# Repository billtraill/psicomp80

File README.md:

# PSI COMP80

**The web pages: [billtraill.github.io/psicomp80](https://billtraill.github.io/psicomp80/)**: screens, an emulator to run in your browser, annotated ROM listings, a LISP, and the hardware in three versions.

The PSI COMP80 is a Z80 computer designed by J. H. Adams. It was published as a build-it-yourself series, "A scientific computer", in *Wireless World* from April to September 1979, and Powertran sold it as a kit. It has a 64 × 32 character screen, an MM57109 calculator chip for its arithmetic, and BURP, a calculator language, in 3 KB of ROM.

This repository brings it back:
- a MAME driver;
- the ROM, disassembled and annotated;
- twenty more ROMs written for it: FORTH, LISP, Tiny BASIC, Logo, CHIP-8, FOCAL, PILOT, a Z80 assembler and disassembler (ZASM), Prolog, VTL-2, Mouse, Befunge, a spreadsheet (CALC), TRAC, a PL/0 compiler, BF, a line editor (ED), a card-file database (FILE), an adventure engine (QUEST) and APL;
- its programs and the 1980 floppy disc system;
- a web emulator;
- the original board redrawn in KiCad, plus two new versions that run the same ROMs on current parts.

## The web pages

| Page | What it is |
|---|---|
| [PSI COMP80 Screens](https://billtraill.github.io/psicomp80/screenshots.html) | What it looked like: the monitor, BURP, FORTH, LISP, the Game of Life, the articles' pictures |
| [Emulator](https://billtraill.github.io/psicomp80/emulator.html) | The COMP80 in the browser, with all twenty-one ROMs and their example programs |
| [ROM Listings](https://billtraill.github.io/psicomp80/roms.html) | The monitor and the twenty-one languages and programs, annotated, with hex dumps |
| [COMP80 LISP](https://billtraill.github.io/psicomp80/lisp.html) | The LISP that takes BURP's place in the ROM, with examples |
| [Original hardware](https://billtraill.github.io/psicomp80/hardware.html) | The 1979 main board redrawn from the kit: every part and every circuit |
| [v2 hardware](https://billtraill.github.io/psicomp80/hardware_v2.html) | One RP2350 microcontroller, HDMI, a USB keyboard, ROMs and tapes on microSD |
| [v3 hardware](https://billtraill.github.io/psicomp80/hardware_v3.html) | The machine in logic in an Artix-7 FPGA, with HDMI and DisplayPort over USB-C |

Each page is a single self-contained HTML file in this folder, so they also work offline straight from a clone.

## What's in this repository

| Where | What |
|---|---|
| `psicomp80.cpp`, `mame/` | The MAME driver, and the files and script that install it into a MAME checkout; `mame/test_session.lua` types a test session at any of the ROMs |
| `psicomp80.rom`, `psicomp80_*.rom` | The ROM images: the monitor with BURP, or one of the other twenty, in the top 2 KB; each also as `…_ks.rom`, with the key-safe monitor |
| `rom/` | The annotated disassembly (`psicomp80.asm`), which assembles back to the ROM byte for byte, and the listings page |
| `burp/`, `forth/`, `lisp/` | BURP, FORTH and LISP: notes, sources, examples and tests |
| `basic/`, `logo/`, `chip8/`, `focal/`, `pilot/`, `zasm/`, `prolog/` | The other languages, each with its source, `build.sh`, README, examples and tests |
| `vtl/`, `mouse/`, `befunge/`, `sheet/`, `trac/`, `pl0/`, `bf/`, `ed/`, `db/`, `adv/`, `apl/` | The ROMs under Other on the emulator page, laid out the same way |
| `life/`, `pictures/` | The Game of Life and the articles' pictures, as programs and tapes |
| `storm/`, `plasma/`, `dump/`, `fire/`, `banner/` | More machine code: Storm (a shooting game), a plasma, a memory viewer, a fire effect and a scrolling banner |
| `disk/` | The floppy disc extension (October and December 1980): disc image and software |
| `web/` | The web emulator's source and build |
| `hardware/` | The original board in KiCad, and the hardware page |
| `hardware_v2/` | The RP2350 version: board, firmware and tests |
| `hardware_v3/` | The FPGA version: board, Verilog, firmware, simulations, and the Vivado and setup guides |
| `info/` | The *Wireless World* articles and the MM57109 data sheet |
| `c80.sh`, `start.lua`, `autorun.lua` | Start MAME straight into a program, or load a tape |
| `monitor_cmds.md` | The monitor's commands |
| `old/`, `early_versions/` | Earlier disassemblies and driver versions |

## Running it in MAME

1. Get the MAME source next to this folder, at `~/localdev/mame` (or set `MAME_DIR`):

   ```bash
   git clone https://github.com/mamedev/mame.git ~/localdev/mame
   ```

2. Copy the driver, the ROMs and the build scripts into it:

   ```bash
   mame/install.sh
   ```

3. Build just this driver, in the MAME folder:

   ```bash
   cd ~/localdev/mame && ./build.sh
   ```

   `mame/BUILD.md` has the full notes: SDL2 on macOS, and regenerating the project files after the checkout moves.

4. Run it under the debugger with `./run.sh`. Useful debugger commands:

   ```
   bpset 38           ; break on the IM 1 interrupt handler
   wpset 8000,800,w   ; watch writes to the screen (0x800 bytes at 0x8000)
   ```

After changing a ROM, `python3 calc_rom_crc.py` gives the checksum that goes in `psicomp80.cpp`. `convert_to_rom.py` made the first ROM image from the magazine's hex listing.

## Starting a program directly

`c80.sh` starts MAME straight into a program. It copies the program into memory and types the command for you, with no tape to load. Extra MAME options can go after the name.

```bash
./c80.sh life       # Game of Life
./c80.sh boat       # Fig. 22(b) sailing boat
./c80.sh schmitt    # Fig. 22(a) Schmitt trigger circuit
./c80.sh cover      # the screen on the kit leaflet's cover
./c80.sh alph       # the monitor's ALPH character set test
./c80.sh list       # LIST 1000 with Life loaded
./c80.sh disk       # floppy disc software, program disc in the drive
./c80.sh forth      # FORTH ROM (FORTH in place of BURP)
./c80.sh forthlife  # Game of Life typed into FORTH
./c80.sh mandel     # Mandelbrot set typed into FORTH
./c80.sh lisp       # LISP ROM (LISP in place of BURP)
./c80.sh deriv      # symbolic differentiation typed into LISP
./c80.sh hanoi      # Towers of Hanoi typed into LISP
./c80.sh queens     # eight queens typed into LISP
./c80.sh ready      # just the monitor
```

The [screens page](https://billtraill.github.io/psicomp80/screenshots.html) shows what each one looks like.

## BURP

BURP, the original language, runs. At READY type `MOV 0BB50C000C00`, then `^` (RS), then `RUN 5` and a space for the articles' sample program. [`burp/README.md`](burp/README.md) has the walkthrough, the tests, and what was fixed to make it run: the MM57109 model, the interrupts, and one misread ROM byte.

## FORTH and LISP

`psicomp80_forth.rom` and `psicomp80_lisp.rom` replace BURP with a small FORTH or LISP and leave the monitor unchanged. The driver offers them as BIOS options, with BURP as the default:

```bash
cd ~/localdev/mame && ./mamed psicomp80 -bios forth
```

```bash
cd ~/localdev/mame && ./mamed psicomp80 -bios lisp
```

Then press `^` (RS) at READY, as for BURP. See [`forth/README.md`](forth/README.md), [`lisp/README.md`](lisp/README.md) and the [LISP page](https://billtraill.github.io/psicomp80/lisp.html).

## The key-safe monitor

The 1979 monitor takes a key only while the CPU waits for one in a HALT. A key that comes at any other moment restarts the monitor, so a key stops a running program, and a game that reads keys while it runs can be restarted by one. Every ROM also comes with a key-safe monitor, made for this project, which ignores such a key instead and lets the program carry on. The ROM images are `psicomp80_ks.rom` and `psicomp80_<lang>_ks.rom`, and the driver's BIOS names end in `ks`:

```bash
cd ~/localdev/mame && ./mamed psicomp80 -bios pl0ks
```

With it a running program can only be stopped with RESET (F3 in MAME, Esc on the web page), and keys pressed while a program is busy are lost rather than restarting it. The web emulator has the same choice under Monitor. The change is the keyboard handler at 0066, with ten bytes found by moving the code at 0095–012F up into the free bytes at 0130; the entry points the languages use are where they were. See [`rom/README.md`](rom/README.md).

## Tapes

Each tape loads at 1000 and runs with `RUN 1000`. `autorun.lua` loads the mounted tape fast-forwarded, checks it against the `.bin` next to the `.wav`, retries a bad load, and types `RUN 1000`. Don't touch the keyboard until the program starts.

```bash
cd ~/localdev/mame && ./mamed psicomp80 -cass ~/localdev/psicomp80/life/life.wav -autoboot_script ~/localdev/psicomp80/autorun.lua
```

The other tapes are `pictures/boat.wav` (Fig. 22(b)), `pictures/schmitt.wav` (Fig. 22(a)) and `pictures/cover.wav` (the kit leaflet's cover). In Life, R starts a new random board, P pauses and S goes back to the monitor (see [`life/README.md`](life/README.md)). For the pictures, any key goes back to the monitor.

To load a tape by hand: type `READ 1000`, then Tab → Tape Control → Play (Tab again to close the menu). Wait for the tape to stop, press any key, then type `RUN 1000`.

## Floppy disc

The floppy disc extension from the October and December 1980 articles: an FD1771 controller and an 8 inch IBM 3740 drive (77 tracks × 26 sectors × 128 bytes). `disk/programs.img` is a disc with all the programs on it.

```bash
./c80.sh disk
```

Then use `READ` followed by the destination, track, sector and number of sectors, each followed by a space. For example, `READ 1000 1 1 6` then `RUN 1000` runs the Game of Life, and `READ 8000 0 1 16` shows the disc's catalogue. Type `RUN 1D00` before each disc command.

`FORMAT` builds a track image at C000, which needs the 32 KB memory expansion. That machine is `psicomp80x` ("COMP80 with 32K expansion"):

```bash
./c80.sh 32k disk
```

See [`disk/README.md`](disk/README.md).

## In a web browser

[`emulator.html`](https://billtraill.github.io/psicomp80/emulator.html) is the COMP80 as a single web page. It switches between the BURP, FORTH and LISP ROMs, runs all the example programs by typing them in for you, and has a help page for each language. It has no tape or disc. Rebuild it with `python3 web/build.py`; see [`web/README.md`](web/README.md).

## ROM listings

[`rom/psicomp80.asm`](rom/psicomp80.asm) is the annotated disassembly of `psicomp80.rom` (the monitor and BURP), and it assembles back to the ROM byte for byte. The [listings page](https://billtraill.github.io/psicomp80/roms.html) shows it with the FORTH and LISP sources, each name and jump a link, and hex dumps of all three ROMs. `rom/build.sh` checks the sources against the ROMs and rebuilds the page. See [`rom/README.md`](rom/README.md).

## Hardware

- **The original** ([page](https://billtraill.github.io/psicomp80/hardware.html), [`hardware/`](hardware/)): the 1979 main board in KiCad, with copper routed or traced from the kit artwork. The page talks through each circuit and lists every part. Rebuild it with `python3 hardware/tools/make_hardware_page.py`.
- **v2** ([page](https://billtraill.github.io/psicomp80/hardware_v2.html), [`hardware_v2/`](hardware_v2/)): one RP2350 microcontroller emulates the machine. It has HDMI, a USB keyboard, ROMs and tapes on microSD, and USB-C power. Board, firmware and tests.
- **v3** ([page](https://billtraill.github.io/psicomp80/hardware_v3.html), [`hardware_v3/`](hardware_v3/)): the machine in logic in an Artix-7 XC7A100T FPGA. It has HDMI, a USB keyboard, microSD, USB-C power, and DisplayPort over a second USB-C socket. [`VIVADO_TODO.md`](hardware_v3/VIVADO_TODO.md) has the build steps still to do, and [`SETUP.md`](hardware_v3/SETUP.md) covers setting up a board.

## Things to try

- The monitor's commands are in [`monitor_cmds.md`](monitor_cmds.md). `ALPH` shows the character set; `LIST 1000` lists memory; `ALT` changes it.
- `RUN 01B6` was once thought to be a guessing game. It's actually a jump into the middle of the monitor's register display routine (01AA), which is why it behaves oddly.

## To do

- [ ] **v3: make and bring up a board** ([`SETUP.md`](hardware_v3/SETUP.md)). Check the USB-C monitor with the plug both ways up: the lane order and AUX polarity for each orientation were worked out from the specifications, not measured.
- [ ] **v2: make and test a board.** The firmware's machine matches the web emulator in host tests, but it hasn't run on hardware.
- [ ] **v2: fit a flat USB-A socket.** The Würth 614004134726 stands upright; v3 now uses a flat Molex 67643.
- [ ] **v3, optional: power from the video USB-C.** Today only J1 powers the board. Taking power from J7 needs a power mux, overvoltage protection, and firmware that asks the monitor for 5 V and swaps data roles.
- [ ] **Web emulator, optional: tapes and discs.** Programs are copied into memory instead.

Done:
- [x] **v3: build the bitstream.** Vivado 2026.1 builds it and every clock meets timing; [`hardware_v3/VIVADO_TODO.md`](hardware_v3/VIVADO_TODO.md) has the results.

Done from the original list:
- [x] Worked out how the monitor parses commands: `LIST 1000` works, and the reason `RUN 01B6` misbehaves is above.
- [x] Fixed the keyboard: the driver latches each key and pulses NMI, as the 1979 keyboard did.
- [x] Documented the monitor commands ([`monitor_cmds.md`](monitor_cmds.md)).
- [x] Disassembled and annotated the ROM ([`rom/psicomp80.asm`](rom/psicomp80.asm)).
- [x] Put the project in git, on GitHub with web pages.

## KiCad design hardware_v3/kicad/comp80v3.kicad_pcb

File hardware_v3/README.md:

# COMP80 v3: the COMP80 in an Artix-7 FPGA

The COMP80 built again in logic, in an AMD Artix-7 XC7A100T. A Verilog Z80 and its
64 KB of memory, the I/O ports, the keyboard latch and NMI, and the display are all
logic. A PicoRV32 RISC-V soft processor in the same FPGA reads the microSD card,
models the MM57109 and the cassette, and turns USB keyboard reports into key codes.
The outside is v2's, HDMI, USB keyboard, microSD and USB-C power, plus a second
USB-C socket that sends the screen to a USB-C monitor as DisplayPort. The web page is
`../hardware_v3.html`.

The bitstream builds in Vivado and meets timing; no board has been made yet.
`VIVADO_TODO.md` has the build steps, what the reports showed and the bring-up
checklist. `SETUP.md` covers a built board: programming it, the microSD card, the keys,
the serial console and the USB-C monitor.

| Folder | What's in it |
|---|---|
| `rtl/` | The logic: `top.v`, `comp80_machine.v` (the COMP80), `tv80c.v` (TV80 with a clock enable), `video.v`, `hdmi_out.v`, `dp_out.v` (DisplayPort), `soc.v` (PicoRV32 and its registers), `spi_master.v`, `font.hex`, and `comp80v3.xdc` (pins, made by `tools/design.py`). `dp_comp80_source.v` and `dp_transceivers.v` are generated by `tools/make_dp_source.py` and `tools/make_dp_bank.py` |
| `firmware/` | The soft processor's firmware: `main.c`, `pd.c` (USB Power Delivery and DisplayPort alternate mode through the FUSB302), `sd_spi.c`, `hw.h`, plus v2's `mm57109.c`, `tape.c` and `storage.c`. `firmware.hex` is the built RAM image |
| `sim/` | Verilator and Icarus Verilog testbenches |
| `vivado/build.tcl` | The Vivado build: bitstream and flash image |
| `tools/` | `design.py` (the board), `make_board.py` (KiCad), `fetch.sh` (outside HDL), `synth.sh` (yosys), `make_font.py`, `make_page.py` |
| `kicad/` | The KiCad 10 board: six layers, routed and filled. KiCad's DRC: no errors |
| `netlist.json`, `bom.csv` | The connections and the parts list |
| `fab/` | Files for a board house: Gerbers and drill files, a PCBWay BOM, pick-and-place and an assembly drawing, with the quote settings in `fab/README.md`. Rebuilt by `tools/make_fab.py` |

Outside HDL, fetched into `build/` by `tools/fetch.sh` at fixed commits: TV80 (MIT),
PicoRV32 (ISC), usb_hid_host (Apache-2.0), DisplayPort_Verilog (MIT), and FatFs for
the firmware.

## Tests

```bash
cd hardware_v3/sim && make test
```

This runs LISP, FORTH and BURP sessions on the logic and on v2's C core and compares
the screens: they match. It takes about a minute each.

```bash
cd hardware_v3/sim && make boot
```

This boots the soft processor's firmware with the machine. It prints `COMP80 v3`,
loads the built-in ROM and reaches READY.

```bash
cd hardware_v3/sim && iverilog -g2012 -DSIM -o video_tb video_tb.v ../rtl/video.v ../rtl/hdmi_out.v && vvp video_tb +screen=screen.hex
```

This draws one HDMI frame from a 2 KB screen dump (v2's `host/session` writes one
with `SCREEN=file`) and checks every TMDS symbol.

```bash
cd hardware_v3/sim && iverilog -g2012 -o dp_tb dp_tb.v ../rtl/dp_comp80_source.v ../build/DisplayPort_Verilog/src/test_streams/insert_main_stream_attrbutes_one_channel.v && vvp dp_tb +screen=screen.hex && python3 dp_decode.py screen.hex
```

The same for DisplayPort: it runs the COMP80 DisplayPort source and the core's
stream-attribute inserter on the screen dump and `dp_decode.py` turns the lane symbols back into a frame
(`dp_frame.png`) and compares it pixel by pixel.

```bash
sh hardware_v3/tools/synth.sh
```

This runs yosys for the XC7A100T. The design comes to about 5,900 LUTs, 3,600
flip-flops and 50 block RAMs, plus the four GTP transceivers.

## The board

110 × 84 mm, six layers: signals outside, then ground, 3.3 V, 1.0 V and 1.8 V planes,
with islands under the BGA for the transceivers' 1.0 V and 1.2 V and for bank 35's
2.5 V. The
XC7A100T in FGG484, a 16 MB SPI flash for its configuration, a 100 MHz oscillator,
and three TLV62569 bucks (1.0, 1.8, 3.3 V) from USB-C. It has HDMI straight from
TMDS_33 outputs, a USB-A socket for the keyboard, microSD, a 6-pin JTAG header, a
serial header, RESET and PROG buttons, and HALT and DONE LEDs.

The second USB-C socket (J7) is for a monitor. A FUSB302B handles USB Power
Delivery, a TPS2051C switches 5 V out to the monitor, and the FPGA's four GTP
transceivers drive the socket's four high-speed pairs from a 135 MHz oscillator.
Two LDOs give 2.5 V (the bank with the AUX channel) and 1.2 V (MGTAVTT).

Along the bottom edge, in silkscreen: the COMP80's screen as drawn on the cover of
the kit leaflet, the name and version, and its line from the 1979 original through
v2.

```bash
cd hardware_v3/tools && python3 design.py
```

```bash
cd hardware_v3/tools && /Applications/KiCad/KiCad.app/Contents/Frameworks/Python.framework/Versions/Current/bin/python3 make_board.py
```

```bash
cd hardware/tools && /Applications/KiCad/KiCad.app/Contents/Frameworks/Python.framework/Versions/Current/bin/python3 route_board.py --pcb ../../hardware_v3/kicad/comp80v3.kicad_pcb --freerouting freerouting-2.5.0.jar --java /opt/homebrew/opt/openjdk/bin/java --passes 60
```

Then run it again with `--keep` added, which keeps what's routed and works on the
rest. `make_board.py` lays the hardest parts first: the BGA's breakout vias, the
plane and island vias, J7's escape vias, and HDMI's ground comb and escape vias.
Freerouting usually leaves a few connections; run KiCad's DRC to list them, and
finish each net with the grid router at v3's clearances (0.3 mm tracks for VBUS):

```bash
cd hardware/tools && GRID=0.05 CLEAR=0.15 TRACK=0.15 /Applications/KiCad/KiCad.app/Contents/Frameworks/Python.framework/Versions/Current/bin/python3 finish_routes.py --pcb ../../hardware_v3/kicad/comp80v3.kicad_pcb VIDEO_VBUS
```

## Firmware

```bash
cd hardware_v3/firmware && make
```

This needs a RISC-V GCC (xPack `riscv-none-elf-gcc` 15) and `build/fatfs`. It writes
`firmware.hex`, which goes into the bitstream as the soft processor's RAM contents.

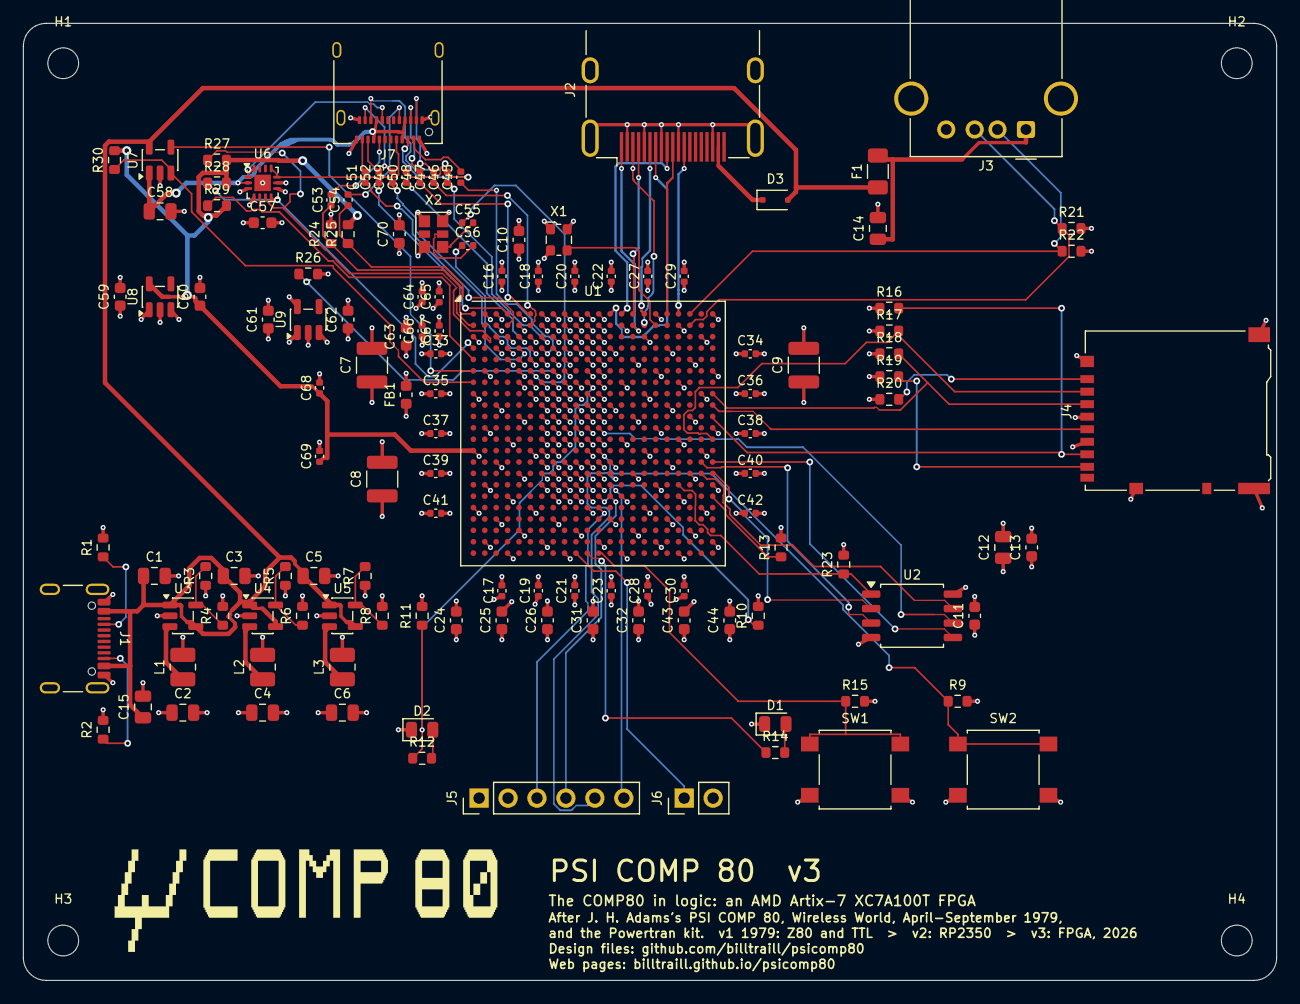
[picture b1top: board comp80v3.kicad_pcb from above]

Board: 6 copper layers, 110.0 x 84.0 mm, 132 parts (0 on the bottom side), 87 nets.

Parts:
C1, C3, C5, C12, C14, C15, C58: 10u; C_0805_2012Metric
C2, C4, C6: 22u; C_0805_2012Metric
C7: 100u; C_1210_3225Metric
C8, C9: 47u; C_1210_3225Metric
C10, C11, C13, C70: 100n; C_0603_1608Metric
C16, C17, C18, C19, C20, C21, C22, C23, C27, C28, C29, C30, C33, C34, C35, C36, C37, C38, C39, C40, C41, C42: 470n; C_0402_1005Metric
C24, C25, C26, C31, C32, C43, C44, C62, C63: 4.7u; C_0603_1608Metric
C45, C46, C47, C48, C49, C50, C51, C52, C53, C54, C55, C56, C64, C65, C66, C67, C68, C69: 100n; C_0402_1005Metric
C57, C59, C60, C61: 1u; C_0603_1608Metric
D1: HALT; LED_0805_2012Metric
D2: DONE; LED_0805_2012Metric
D3: BAT54J; D_SOD-323F
F1: 500mA; Fuse_1206_3216Metric
FB1: 220R@100MHz; L_0603_1608Metric
H1, H2, H3, H4: M2.5; MountingHole_2.7mm_M2.5
J1: USB-C; USB_C_Receptacle_GCT_USB4105-xx-A_16P_TopMnt_Horizontal
J2: HDMI; HDMI_A_Molex_208658-1001_Horizontal
J3: USB-A; USB_A_Molex_67643_Horizontal
J4: microSD; microSD_HC_Hirose_DM3AT-SF-PEJM5
J5: JTAG; PinHeader_1x06_P2.54mm_Vertical
J6: SERIAL; PinHeader_1x02_P2.54mm_Vertical
J7: USB-C VIDEO; USB_C_Receptacle_Amphenol_12401610E4-2A
L1, L2, L3: 2.2uH; L_1008_2520Metric
R1, R2: 5.1k; R_0603_1608Metric
R3, R5: 200k; R_0603_1608Metric
R4: 301k; R_0603_1608Metric
R6, R8, R24, R25: 100k; R_0603_1608Metric
R7: 453k; R_0603_1608Metric
R9, R10, R27, R28, R29: 4.7k; R_0603_1608Metric
R11, R14: 330R; R_0603_1608Metric
R12, R13: 1k; R_0603_1608Metric
R15, R16, R17, R18, R19, R20, R23, R30: 10k; R_0603_1608Metric
R21, R22: 15k; R_0603_1608Metric
R26: 100R 1%; R_0603_1608Metric
SW1: RESET; SW_SPST_B3S-1000
SW2: PROG; SW_SPST_B3S-1000
U1: XC7A100T-1FGG484C; Xilinx_FGG484
U2: IS25LP128F; SOIC-8_5.3x5.3mm_P1.27mm
U3, U4, U5: TLV62569DBV; SOT-23-5
U6: FUSB302B; WQFN-14-1EP_2.5x2.5mm_P0.5mm_EP1.45x1.45mm
U7: TPS2051C; SOT-23-5
U8: TLV75525; SOT-23-5
U9: TLV75512; SOT-23-5
X1: 100MHz; Oscillator_SMD_ECS_2520MV-xxx-xx-4Pin_2.5x2.0mm
X2: 135MHz; Oscillator_SMD_SiTime_SiT9121-6Pin_3.2x2.5mm

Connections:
+1V0: C2.1, C7.1, C16.1, C17.1, C18.1, C19.1, C20.1, C21.1, C22.1, C23.1, C24.1, C25.1, C26.1, FB1.1, L1.2, R3.1, U1.H8, U1.H10, U1.J7, U1.J9, U1.J11, U1.K8, U1.L7, U1.L11, U1.M8, U1.N7, U1.N11, U1.P8, U1.P10, U1.R7, U1.R9, U1.T8, U1.T10
+1V0_MGT: C63.1, C64.1, C65.1, FB1.2, U1.D6, U1.D10, U1.E8, U1.F7, U1.F9
+1V2: C62.1, C66.1, C67.1, R26.2, U1.B5, U1.B7, U1.B9, U1.B11, U1.C4, U1.C8, U9.5
+1V8: C4.1, C8.1, C27.1, C28.1, C29.1, C30.1, C31.1, C32.1, L2.2, R5.1, U1.H12, U1.K10, U1.K12, U1.M12, U1.P12, U1.R11
+2V5: C60.1, C68.1, C69.1, R25.2, R27.2, R28.2, R29.2, R30.2, U1.C1, U1.F2, U1.H6, U1.J3, U1.M4, U1.N1, U8.5
+3V3: C6.1, C9.1, C10.1, C11.1, C12.1, C13.1, C33.1, C34.1, C35.1, C36.1, C37.1, C38.1, C39.1, C40.1, C41.1, C42.1, C43.1, C44.1, C57.1, C59.1, C61.1, C70.1, J4.4, J5.1, L3.2, R7.1, R9.2, R10.2, R11.2, R13.2, R15.2, R16.1, R17.1, R18.1, R19.1, R20.1, R23.2, U1.A17, U1.AA7, U1.AA17, U1.AB4, U1.AB14, U1.B14, U1.C21, U1.D18, U1.E15, U1.F12, U1.F22, U1.G19, U1.H16, U1.J13, U1.K20, U1.L17, U1.M14, U1.N21, U1.P18, U1.R5, U1.R15, U1.T2, U1.T12, U1.T22, U1.U8, U1.U11, U1.U19, U1.V6, U1.V16, U1.W3, U1.W13, U1.Y10, U1.Y20, U2.8, U6.3, U6.4, U8.1, U8.3, U9.1, U9.3, X1.1, X1.4, X2.1, X2.6
+5V: C1.1, C3.1, C5.1, C15.1, D3.2, F1.1, J1.A4, J1.A9, J1.B4, J1.B9, U3.1, U3.4, U4.1, U4.4, U5.1, U5.4, U7.5
AUX_N_FPGA: C54.1, R25.1, U1.A1
AUX_P_FPGA: C53.1, R24.1, U1.B1
CLK100: U1.B17, X1.3
DONE: R11.1, R12.1, U1.G11
DONE_LED: D2.2, R12.2
DP0_N: C46.2, J7.A3
DP0_N_FPGA: C46.1, U1.C7
DP0_P: C45.2, J7.A2
DP0_P_FPGA: C45.1, U1.D7
DP1_N: C48.2, J7.B10
DP1_N_FPGA: C48.1, U1.A6
DP1_P: C47.2, J7.B11
DP1_P_FPGA: C47.1, U1.B6
DP2_N: C50.2, J7.B3
DP2_N_FPGA: C50.1, U1.C5
DP2_P: C49.2, J7.B2
DP2_P_FPGA: C49.1, U1.D5
DP3_N: C52.2, J7.A10
DP3_N_FPGA: C52.1, U1.A4
DP3_P: C51.2, J7.A11
DP3_P_FPGA: C51.1, U1.B4
FB_1V0: R3.2, R4.1, U3.5
FB_1V8: R5.2, R6.1, U4.5
FB_3V3: R7.2, R8.1, U5.5
FLASH_CS: R23.1, U1.T19, U2.1
FLASH_IO0: U1.P22, U2.5
FLASH_IO1: U1.R22, U2.2
FLASH_IO2: U1.P21, U2.3
FLASH_IO3: U1.R21, U2.7
FLASH_SCK: U1.L12, U2.6
GND: C1.2, C2.2, C3.2, C4.2, C5.2, C6.2, C7.2, C8.2, C9.2, C10.2, C11.2, C12.2, C13.2, C14.2, C15.2, C16.2, C17.2, C18.2, C19.2, C20.2, C21.2, C22.2, C23.2, C24.2, C25.2, C26.2, C27.2, C28.2, C29.2, C30.2, C31.2, C32.2, C33.2, C34.2, C35.2, C36.2, C37.2, C38.2, C39.2, C40.2, C41.2, C42.2, C43.2, C44.2, C57.2, C58.2, C59.2, C60.2, C61.2, C62.2, C63.2, C64.2, C65.2, C66.2, C67.2, C68.2, C69.2, C70.2, D1.1, D2.1, J1.A1, J1.A12, J1.B1, J1.B12, J1.SH, J2.2, J2.5, J2.8, J2.11, J2.17, J2.SH, J3.4, J3.SH, J4.6, J4.SH, J5.2, J6.2, J7.A1, J7.A12, J7.B1, J7.B12, J7.SH, R1.2, R2.2, R4.2, R6.2, R8.2, R21.2, R22.2, R24.2, SW1.2, SW2.2, U1.A2, U1.A3, U1.A5, U1.A7, U1.A8, U1.A9, U1.A10, U1.A11, U1.A12, U1.A22, U1.AA2, U1.AA12, U1.AA22, U1.AB9, U1.AB19, U1.B3, U1.B8, U1.B10, U1.B12, U1.B19, U1.C3, U1.C6, U1.C9, U1.C10, U1.C11, U1.C12, U1.C16, U1.D3, U1.D4, U1.D8, U1.D9, U1.D11, U1.D12, U1.D13, U1.E4, U1.E5, U1.E7, U1.E9, U1.E11, U1.E12, U1.E20, U1.F5, U1.F11, U1.F17, U1.G5, U1.G6, U1.G7, U1.G8, U1.G9, U1.G10, U1.G12, U1.G14, U1.H1, U1.H7, U1.H9, U1.H11, U1.H21, U1.J8, U1.J10, U1.J12, U1.J18, U1.K5, U1.K7, U1.K9, U1.K11, U1.K15, U1.L2, U1.L8, U1.L9, U1.L10, U1.L22, U1.M7, U1.M9, U1.M10, U1.M11, U1.M19, U1.N6, U1.N8, U1.N16, U1.P3, U1.P7, U1.P9, U1.P11, U1.P13, U1.R8, U1.R10, U1.R12, U1.R20, U1.T7, U1.T9, U1.T11, U1.T17, U1.U4, U1.U9, U1.U10, U1.U14, U1.V1, U1.V11, U1.V21, U1.W8, U1.W18, U1.Y5, U1.Y15, U2.4, U3.2, U4.2, U5.2, U6.8, U6.9, U6.15, U7.2, U8.2, U9.2, X1.2, X2.3
HALT_LED: R14.1, U1.AB11
HALT_LED_A: D1.2, R14.2
HDMI_5V: D3.1, J2.18
INIT_B: R10.1, U1.U12
MGTRREF: R26.1, U1.F8
PD_INT_N: R29.1, U1.E1, U6.5
PD_SCL: R27.1, U1.C2, U6.6
PD_SDA: R28.1, U1.D1, U6.7
PROGRAM_B: R9.1, SW2.1, U1.N12
PUDC_B: R13.1, U1.U22
REFCLK_N: C56.2, X2.5
REFCLK_N_FPGA: C56.1, U1.E6
REFCLK_P: C55.2, X2.4
REFCLK_P_FPGA: C55.1, U1.F6
RESET_N: R15.1, SW1.1, U1.AB12
SBU1: C53.2, J7.A8
SBU2: C54.2, J7.B8
SD_CS: J4.2, R17.2, U1.M22
SD_DAT1: J4.8, R19.2
SD_DAT2: J4.1, R20.2
SD_MISO: J4.7, R16.2, U1.K22
SD_MOSI: J4.3, R18.2, U1.H22
SD_SCK: J4.5, U1.J22
SW_1V0: L1.1, U3.3
SW_1V8: L2.1, U4.3
SW_3V3: L3.1, U5.3
TCK: J5.3, U1.V12
TDI: J5.5, U1.R13
TDO: J5.4, U1.U13
TMDS_CKN: J2.12, U1.A19
TMDS_CKP: J2.10, U1.A18
TMDS_D0N: J2.9, U1.A14
TMDS_D0P: J2.7, U1.A13
TMDS_D1N: J2.6, U1.A16
TMDS_D1P: J2.4, U1.A15
TMDS_D2N: J2.3, U1.B16
TMDS_D2P: J2.1, U1.B15
TMS: J5.6, U1.T13
UART_TX: J6.1, U1.AB10
USBC_CC1: J1.A5, R1.1
USBC_CC2: J1.B5, R2.1
USBH_DM: J3.2, R22.1, U1.A20
USBH_DP: J3.3, R21.1, U1.B20
USBH_VBUS: C14.1, F1.2, J3.1
VBUS_EN: U1.F1, U7.4
VBUS_FLT_N: R30.1, U1.G1, U7.3
VIDEO_CC1: J7.A5, U6.10, U6.11
VIDEO_CC2: J7.B5, U6.1, U6.14
VIDEO_VBUS: C58.1, J7.A4, J7.A9, J7.B4, J7.B9, U6.2, U7.1

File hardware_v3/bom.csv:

Qty,References,Value,Footprint,Part,Description
7,C1 C3 C5 C12 C14 C15 C58,10u,C_0805_2012Metric,,1.0 V regulator input; 1.8 V regulator input; 3.3 V regulator input; Keyboard 5 V; Monitor VBUS; USB-C 5 V in; microSD supply
3,C2 C4 C6,22u,C_0805_2012Metric,,1.0 V regulator output; 1.8 V regulator output; 3.3 V regulator output
1,C7,100u,C_1210_3225Metric,,"FPGA core supply (VCCINT, VCCBRAM) bulk"
2,C8 C9,47u,C_1210_3225Metric,,FPGA auxiliary supply (VCCAUX) bulk; I/O supply (VCCO) bulk
4,C10 C11 C13 C70,100n,C_0603_1608Metric,,135 MHz oscillator decoupling; Flash decoupling; Oscillator decoupling; microSD decoupling
22,C16 C17 C18 C19 C20 C21 C22 C23 C27 C28 C29 C30 C33 C34 C35 C36 C37 C38 C39 C40 C41 C42,470n,C_0402_1005Metric,,"FPGA I/O (VCCO) decoupling; FPGA auxiliary (VCCAUX) decoupling; FPGA core (VCCINT, VCCBRAM) decoupling"
9,C24 C25 C26 C31 C32 C43 C44 C62 C63,4.7u,C_0603_1608Metric,,"1.2 V regulator output, MGTAVTT; FPGA I/O (VCCO) decoupling; FPGA auxiliary (VCCAUX) decoupling; FPGA core (VCCINT, VCCBRAM) decoupling; MGTAVCC, after the ferrite"
18,C45 C46 C47 C48 C49 C50 C51 C52 C53 C54 C55 C56 C64 C65 C66 C67 C68 C69,100n,C_0402_1005Metric,,"135 MHz reference AC coupling, +; 135 MHz reference AC coupling, -; AUX channel AC coupling, SBU1; AUX channel AC coupling, SBU2; DisplayPort lane AC coupling, J7 RX1+; DisplayPort lane AC coupling, J7 RX1-; DisplayPort lane AC coupling, J7 RX2+; DisplayPort lane AC coupling, J7 RX2-; DisplayPort lane AC coupling, J7 TX1+; DisplayPort lane AC coupling, J7 TX1-; DisplayPort lane AC coupling, J7 TX2+; DisplayPort lane AC coupling, J7 TX2-; FPGA MGTAVCC decoupling; FPGA MGTAVTT decoupling; FPGA bank 35 VCCO decoupling"
4,C57 C59 C60 C61,1u,C_0603_1608Metric,,1.2 V regulator input (3.3 V); 2.5 V regulator input; 2.5 V regulator output; FUSB302 supply
1,D1,HALT,LED_0805_2012Metric,"red LED, 0805","Lit while the Z80 is halted, as the original's HALT LED"
1,D2,DONE,LED_0805_2012Metric,"green LED, 0805",Lit once the FPGA has loaded its configuration
1,D3,BAT54J,D_SOD-323F,Nexperia BAT54J,Feeds the HDMI +5 V pin
1,F1,500mA,Fuse_1206_3216Metric,Bourns MF-MSMF050-2,Resettable fuse for the keyboard's 5 V
1,FB1,220R@100MHz,L_0603_1608Metric,Murata BLM18KG221SN1D,Ferrite bead: filters 1.0 V into the transceivers' analogue supply (MGTAVCC)
1,J1,USB-C,USB_C_Receptacle_GCT_USB4105-xx-A_16P_TopMnt_Horizontal,GCT USB4105-GF-A,"Power in, 5 V"
1,J2,HDMI,HDMI_A_Molex_208658-1001_Horizontal,Molex 208658-1001,HDMI type A socket: the display
1,J3,USB-A,USB_A_Molex_67643_Horizontal,Molex 67643-3910,"USB-A socket for the keyboard, lying flat"
1,J4,microSD,microSD_HC_Hirose_DM3AT-SF-PEJM5,Hirose DM3AT-SF-PEJM5,microSD socket: ROM images and tapes
1,J5,JTAG,PinHeader_1x06_P2.54mm_Vertical,"0.1 in header, 6 way","JTAG for Vivado: VREF, GND, TCK, TDO, TDI, TMS, the order of Digilent's 6-pin cables"
1,J6,SERIAL,PinHeader_1x02_P2.54mm_Vertical,"0.1 in header, 2 way",The soft processor's serial console out (115200 baud) and ground
1,J7,USB-C VIDEO,USB_C_Receptacle_Amphenol_12401610E4-2A,Amphenol 12401610E4-2A,Video out: DisplayPort alternate mode to a USB-C monitor
1,L1,2.2uH,L_1008_2520Metric,Murata DFE252012F-2R2M,Inductor for the 1.0 V regulator
1,L2,2.2uH,L_1008_2520Metric,Murata DFE252012F-2R2M,Inductor for the 1.8 V regulator
1,L3,2.2uH,L_1008_2520Metric,Murata DFE252012F-2R2M,Inductor for the 3.3 V regulator
2,R1 R2,5.1k,R_0603_1608Metric,,USB-C CC1: asks the supply for 5 V; USB-C CC2: asks the supply for 5 V
2,R3 R5,200k,R_0603_1608Metric,,"1.0 V regulator feedback, top; 1.8 V regulator feedback, top"
1,R4,301k,R_0603_1608Metric,,"1.0 V regulator feedback, bottom"
4,R6 R8 R24 R25,100k,R_0603_1608Metric,,"1.8 V regulator feedback, bottom; 3.3 V regulator feedback, bottom; AUX+ bias to ground (DisplayPort source); AUX- bias to 2.5 V (DisplayPort source)"
1,R7,453k,R_0603_1608Metric,,"3.3 V regulator feedback, top"
5,R9 R10 R27 R28 R29,4.7k,R_0603_1608Metric,,FUSB302 INT_N pull-up; FUSB302 SCL pull-up; FUSB302 SDA pull-up; INIT_B pull-up; PROGRAM_B pull-up
2,R11 R14,330R,R_0603_1608Metric,,DONE pull-up; HALT LED current
2,R12 R13,1k,R_0603_1608Metric,,DONE LED current; PUDC_B to 3.3 V: I/O pull-ups off while configuring
8,R15 R16 R17 R18 R19 R20 R23 R30,10k,R_0603_1608Metric,,Flash chip select pull-up; RESET button pull-up; VBUS switch fault pull-up; microSD CMD pull-up; microSD DAT0 pull-up; microSD DAT1 pull-up; microSD DAT2 pull-up; microSD DAT3/CS pull-up
2,R21 R22,15k,R_0603_1608Metric,,Keyboard USB D+ pull-down (host side); Keyboard USB D- pull-down (host side)
1,R26,100R 1%,R_0603_1608Metric,,Transceiver termination calibration (MGTRREF to MGTAVTT)
1,SW1,RESET,SW_SPST_B3S-1000,Omron B3S-1000,"Powers the COMP80 on again (the logic, not the FPGA)"
1,SW2,PROG,SW_SPST_B3S-1000,Omron B3S-1000,Pulls PROGRAM_B: the FPGA reloads itself from the flash
1,U1,XC7A100T-1FGG484C,Xilinx_FGG484,AMD XC7A100T-1FGG484C,"FPGA: 101,440 logic cells, 4,860 Kb of block RAM. The whole COMP80 is in here"
1,U2,IS25LP128F,SOIC-8_5.3x5.3mm_P1.27mm,ISSI IS25LP128F-JBLE,16 MB SPI flash: the FPGA's configuration and the soft processor's program
1,U3,TLV62569DBV,SOT-23-5,TI TLV62569DBVR,2 A buck regulator: 1.0 V for the FPGA's core and block RAM
1,U4,TLV62569DBV,SOT-23-5,TI TLV62569DBVR,2 A buck regulator: 1.8 V for the FPGA's auxiliary supply
1,U5,TLV62569DBV,SOT-23-5,TI TLV62569DBVR,2 A buck regulator: 3.3 V for the I/O banks and everything else
1,U6,FUSB302B,WQFN-14-1EP_2.5x2.5mm_P0.5mm_EP1.45x1.45mm,onsemi FUSB302BMPX,USB Power Delivery PHY: agrees DisplayPort alternate mode with the monitor
1,U7,TPS2051C,SOT-23-5,TI TPS2051CDBVR,Current-limited switch: 5 V to the monitor's VBUS
1,U8,TLV75525,SOT-23-5,TI TLV75525PDBVR,2.5 V regulator for I/O bank 35 (the AUX channel's LVDS_25)
1,U9,TLV75512,SOT-23-5,TI TLV75512PDBVR,1.2 V regulator for the transceivers' termination (MGTAVTT)
1,X1,100MHz,Oscillator_SMD_ECS_2520MV-xxx-xx-4Pin_2.5x2.0mm,ECS-2520MV-1000-BN-TR,100 MHz oscillator: the FPGA's clock
1,X2,135MHz,Oscillator_SMD_SiTime_SiT9121-6Pin_3.2x2.5mm,SiTime SiT9121AI-2C3-33E135.000000,135 MHz LVDS oscillator: the transceivers' reference (2.7 Gb/s)

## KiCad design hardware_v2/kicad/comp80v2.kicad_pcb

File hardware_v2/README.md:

# COMP80 v2: the COMP80 on an RP2350

The same computer as the 1979 board, built from current parts: one Raspberry Pi
RP2350A runs the unchanged COMP80 ROM images on an emulated Z80. It shows the
screen over HDMI, takes a USB keyboard, loads ROMs and tapes from a microSD card,
and runs from a USB-C supply. The web page, `../hardware_v2.html`, walks through
it with a zoomable board.

| File | What it is |
|---|---|
| `tools/design.py` | The design: every part, footprint, connection and position. Writes `netlist.json` and `bom.csv` |
| `tools/make_board.py` | Builds `kicad/comp80v2.kicad_pcb` from the design (KiCad's Python): four layers, the parts, the RP2350's supply pins tracked by hand, a via beside every plane pad |
| `kicad/` | The KiCad 10 board, routed and filled. KiCad's DRC: no errors |
| `netlist.json`, `bom.csv` | The connections, and the parts list grouped for ordering |
| `firmware/` | The RP2350 firmware (C, Pico SDK); see its README. `comp80v2.uf2` is a build |
| `tools/make_page.py`, `tools/page_template.html` | Make `../hardware_v2.html` |

## The board

75 × 55 mm, four layers: signals on the outside, ground on In1.Cu, 3.3 V on In2.Cu.

- **U1 RP2350A** at 240 MHz (1.2 V core), with 4 MB of QSPI flash (U2) and a 12 MHz
  crystal. Its on-chip regulator makes the 1.1 V core supply through L1.
- **HDMI** (J2) from the HSTX port, GPIO12–19, through 270 Ω resistors.
- **USB keyboard** (J3) through PIO-USB on GPIO20/21.
- **microSD** (J4) in SPI mode on SPI1, GPIO8–11.
- **USB-C** (J1) for 5 V and for loading firmware; an AP2112K makes 3.3 V.
- RESET and BOOTSEL buttons, a HALT LED, and a debug header with SWD and the serial
  console.

## Regenerating

```bash
cd hardware_v2/tools && python3 design.py
```

```bash
cd hardware_v2/tools && /Applications/KiCad/KiCad.app/Contents/Frameworks/Python.framework/Versions/Current/bin/python3 make_board.py
```

```bash
cd hardware/tools && /Applications/KiCad/KiCad.app/Contents/Frameworks/Python.framework/Versions/Current/bin/python3 route_board.py --pcb ../../hardware_v2/kicad/comp80v2.kicad_pcb --freerouting freerouting-2.5.0.jar --java /opt/homebrew/opt/openjdk/bin/java --passes 80
```

```bash
cd hardware_v2/tools && python3 make_page.py
```

Routing takes about two minutes and is deterministic.

## Not built yet

The board passes KiCad's DRC, and the firmware compiles and passes its tests on a
Mac, but neither has been on real hardware. The RP2350 is a 0.4 mm QFN with 0402
capacitors beside it, so it wants a stencil and reflow or an assembly service.

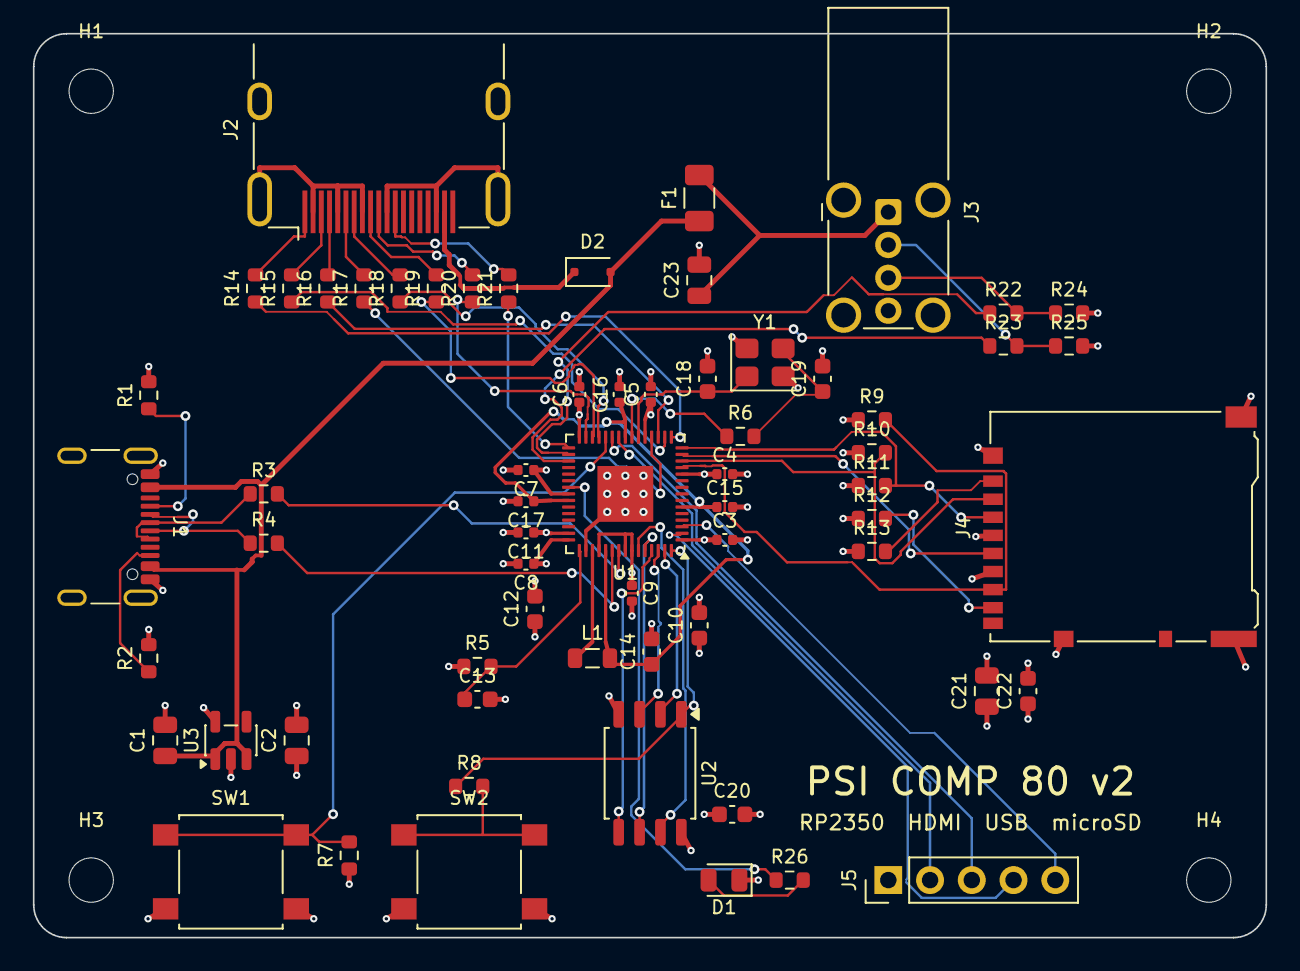
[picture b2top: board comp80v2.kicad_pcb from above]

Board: 4 copper layers, 75.0 x 55.0 mm, 68 parts (0 on the bottom side), 57 nets.

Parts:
C1, C2, C21, C23: 10u; C_0805_2012Metric
C3, C4, C5, C6, C7, C8, C9, C11, C15, C16, C17: 100n; C_0402_1005Metric
C10, C20, C22: 100n; C_0603_1608Metric
C12, C13, C14: 4.7u; C_0603_1608Metric
C18, C19: 15p; C_0603_1608Metric
D1: HALT; LED_0805_2012Metric
D2: BAT54J; D_SOD-323F
F1: 500mA; Fuse_1206_3216Metric
H1, H2, H3, H4: M2.5; MountingHole_2.7mm_M2.5
J1: USB-C; USB_C_Receptacle_GCT_USB4105-xx-A_16P_TopMnt_Horizontal
J2: HDMI; HDMI_A_Molex_208658-1001_Horizontal
J3: USB-A; USB_A_Wuerth_614004134726_Horizontal
J4: microSD; microSD_HC_Hirose_DM3AT-SF-PEJM5
J5: DEBUG; PinHeader_1x05_P2.54mm_Vertical
L1: 3.3uH; L_0805_2012Metric
R1, R2: 5.1k; R_0603_1608Metric
R3, R4, R22, R23: 27R; R_0603_1608Metric
R5: 33R; R_0603_1608Metric
R6, R8: 1k; R_0603_1608Metric
R7, R9, R10, R11, R12, R13: 10k; R_0603_1608Metric
R14, R15, R16, R17, R18, R19, R20, R21: 270R; R_0603_1608Metric
R24, R25: 15k; R_0603_1608Metric
R26: 330R; R_0603_1608Metric
SW1: RESET; SW_SPST_B3S-1000
SW2: BOOTSEL; SW_SPST_B3S-1000
U1: RP2350A; QFN-60-1EP_7x7mm_P0.4mm_EP3.4x3.4mm
U2: W25Q32JV; SOIC-8_5.3x5.3mm_P1.27mm
U3: AP2112K-3.3; SOT-23-5
Y1: 12MHz; Crystal_SMD_3225-4Pin_3.2x2.5mm

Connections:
+1V1: C14.1, C15.1, C16.1, C17.1, L1.2, U1.6, U1.23, U1.39, U1.50
+3V3: C2.1, C3.1, C4.1, C5.1, C6.1, C7.1, C8.1, C9.1, C10.1, C11.1, C12.1, C20.1, C21.1, C22.1, J4.4, R5.1, R7.1, R9.1, R10.1, R11.1, R12.1, R13.1, U1.1, U1.11, U1.20, U1.30, U1.38, U1.44, U1.45, U1.49, U1.53, U1.54, U2.8, U3.5
+5V: C1.1, D2.2, F1.1, J1.A4, J1.A9, J1.B4, J1.B9, U3.1, U3.3
BOOTSEL: R8.2, SW2.1
GND: C1.2, C2.2, C3.2, C4.2, C5.2, C6.2, C7.2, C8.2, C9.2, C10.2, C11.2, C12.2, C13.2, C14.2, C15.2, C16.2, C17.2, C18.2, C19.2, C20.2, C21.2, C22.2, C23.2, D1.1, J1.A1, J1.A12, J1.B1, J1.B12, J1.SH, J2.2, J2.5, J2.8, J2.11, J2.17, J2.SH, J3.4, J3.SH, J4.6, J4.SH, J5.1, R1.2, R2.2, R24.2, R25.2, SW1.2, SW2.2, U1.47, U1.61, U2.4, U3.2, Y1.2, Y1.4
HALT_LED: R26.1, U1.37
HALT_LED_A: D1.2, R26.2
HDMI_5V: D2.1, J2.18
HDMI_CKN_IO: R21.1, U1.31
HDMI_CKP_IO: R20.1, U1.29
HDMI_D0N_IO: R19.1, U1.28
HDMI_D0P_IO: R18.1, U1.27
HDMI_D1N_IO: R17.1, U1.19
HDMI_D1P_IO: R16.1, U1.18
HDMI_D2N_IO: R15.1, U1.17
HDMI_D2P_IO: R14.1, U1.16
QSPI_SCLK: U1.56, U2.6
QSPI_SD0: U1.57, U2.5
QSPI_SD1: U1.59, U2.2
QSPI_SD2: U1.58, U2.3
QSPI_SD3: U1.55, U2.7
QSPI_SS: R8.1, U1.60, U2.1
RUN: R7.2, SW1.1, U1.26
SD_CS: J4.2, R10.2, U1.13
SD_DAT1: J4.8, R12.2
SD_DAT2: J4.1, R13.2
SD_MISO: J4.7, R9.2, U1.12
SD_MOSI: J4.3, R11.2, U1.15
SD_SCK: J4.5, U1.14
SWCLK: J5.2, U1.24
SWDIO: J5.3, U1.25
TMDS_CKN: J2.12, R21.2
TMDS_CKP: J2.10, R20.2
TMDS_D0N: J2.9, R19.2
TMDS_D0P: J2.7, R18.2
TMDS_D1N: J2.6, R17.2
TMDS_D1P: J2.4, R16.2
TMDS_D2N: J2.3, R15.2
TMDS_D2P: J2.1, R14.2
UART_RX: J5.5, U1.3
UART_TX: J5.4, U1.2
USBC_CC1: J1.A5, R1.1
USBC_CC2: J1.B5, R2.1
USBC_DM: J1.A7, J1.B7, R4.1
USBC_DP: J1.A6, J1.B6, R3.1
USBH_DM: J3.2, R23.2, R25.1
USBH_DM_IO: R23.1, U1.33
USBH_DP: J3.3, R22.2, R24.1
USBH_DP_IO: R22.1, U1.32
USBH_VBUS: C23.1, F1.2, J3.1
USB_DM: R4.2, U1.51
USB_DP: R3.2, U1.52
VREG_AVDD: C13.1, R5.2, U1.46
VREG_LX: L1.1, U1.48
XIN: C18.1, U1.21, Y1.1
XOUT: R6.1, U1.22
XTAL: C19.1, R6.2, Y1.3

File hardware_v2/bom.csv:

Qty,References,Value,Footprint,Part,Description
4,C1 C2 C21 C23,10u,C_0805_2012Metric,,"Keyboard 5 V; Regulator input; Regulator output, 3.3 V; microSD supply"
11,C3 C4 C5 C6 C7 C8 C9 C11 C15 C16 C17,100n,C_0402_1005Metric,,RP2350 ADC_AVDD decoupling; RP2350 DVDD decoupling; RP2350 IOVDD decoupling; RP2350 QSPI_IOVDD and USB_OTP_VDD decoupling
3,C10 C20 C22,100n,C_0603_1608Metric,,"Flash decoupling; RP2350 3.3 V decoupling, on the plane; microSD decoupling"
3,C12 C13 C14,4.7u,C_0603_1608Metric,,"Core regulator analogue supply; Core regulator input; Core regulator output, 1.1 V"
2,C18 C19,15p,C_0603_1608Metric,,Crystal load
1,D1,HALT,LED_0805_2012Metric,"red LED, 0805","Lit while the Z80 is halted, as the original's HALT LED"
1,D2,BAT54J,D_SOD-323F,Nexperia BAT54J,"Feeds the HDMI +5 V pin, and stops a display back-powering the board"
1,F1,500mA,Fuse_1206_3216Metric,Bourns MF-MSMF050-2,Resettable fuse for the keyboard's 5 V
1,J1,USB-C,USB_C_Receptacle_GCT_USB4105-xx-A_16P_TopMnt_Horizontal,GCT USB4105-GF-A,"Power in (5 V), and the RP2350's own USB for loading firmware"
1,J2,HDMI,HDMI_A_Molex_208658-1001_Horizontal,Molex 208658-1001,HDMI type A socket: the display
1,J3,USB-A,USB_A_Wuerth_614004134726_Horizontal,Wurth 614004134726,USB-A socket for the keyboard
1,J4,microSD,microSD_HC_Hirose_DM3AT-SF-PEJM5,Hirose DM3AT-SF-PEJM5,microSD socket (push-push): ROM images and tapes
1,J5,DEBUG,PinHeader_1x05_P2.54mm_Vertical,"0.1 in header, 5 way",Debug: SWD and the firmware's serial console (not needed to use the computer)
1,L1,3.3uH,L_0805_2012Metric,Abracon AOTA-B201610S3R3-101-T,Inductor for the RP2350's on-chip 1.1 V core regulator
2,R1 R2,5.1k,R_0603_1608Metric,,USB-C CC1: asks the supply for 5 V; USB-C CC2: asks the supply for 5 V
4,R3 R4 R22 R23,27R,R_0603_1608Metric,,Keyboard USB D+ series resistor; Keyboard USB D- series resistor; USB D+ series resistor; USB D- series resistor
1,R5,33R,R_0603_1608Metric,,Filters the core regulator's analogue supply
2,R6 R8,1k,R_0603_1608Metric,,BOOTSEL: pulls the flash chip select low; Crystal drive limit
6,R7 R9 R10 R11 R12 R13,10k,R_0603_1608Metric,,RUN pull-up; microSD CMD/MOSI pull-up; microSD DAT0/MISO pull-up; microSD DAT1 pull-up; microSD DAT2 pull-up; microSD DAT3/CS pull-up
8,R14 R15 R16 R17 R18 R19 R20 R21,270R,R_0603_1608Metric,,HDMI TMDS CLK+ series resistor; HDMI TMDS CLK- series resistor; HDMI TMDS D0+ series resistor; HDMI TMDS D0- series resistor; HDMI TMDS D1+ series resistor; HDMI TMDS D1- series resistor; HDMI TMDS D2+ series resistor; HDMI TMDS D2- series resistor
2,R24 R25,15k,R_0603_1608Metric,,Keyboard USB D+ pull-down (host side); Keyboard USB D- pull-down (host side)
1,R26,330R,R_0603_1608Metric,,HALT LED current
1,SW1,RESET,SW_SPST_B3S-1000,Omron B3S-1000,Restarts the RP2350: power-on reset of the COMP80
1,SW2,BOOTSEL,SW_SPST_B3S-1000,Omron B3S-1000,"Held during reset, the RP2350 appears as a USB drive for new firmware"
1,U1,RP2350A,QFN-60-1EP_7x7mm_P0.4mm_EP3.4x3.4mm,Raspberry Pi RP2350A,"Microcontroller: two Cortex-M33 cores at up to 150 MHz (run here at 240), 520 KB RAM, HSTX, PIO"
1,U2,W25Q32JV,SOIC-8_5.3x5.3mm_P1.27mm,Winbond W25Q32JVSSIQ,4 MB QSPI flash: holds the firmware
1,U3,AP2112K-3.3,SOT-23-5,Diodes AP2112K-3.3TRG1,"3.3 V 600 mA regulator, from the USB-C 5 V"
1,Y1,12MHz,Crystal_SMD_3225-4Pin_3.2x2.5mm,Abracon ABM8-272-T3,12 MHz crystal for the RP2350's oscillator
